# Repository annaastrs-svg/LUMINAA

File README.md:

LUMINA

SEE PAG !
https://annaastrs-svg.github.io/Lumina-Pag-/

Lumina is a little friend with a module to measure your pulse per minute! It tells you if you're okay, 
if you're very relaxed, or if you're very agitated.

I made this little Tamagotchi pulse meter because I found an oximeter that didn't work at my house,
so I opened it up and tried to make it work with my ESP. I used the TX and it worked, but not in the way I wanted.
I ended up buying an Arduino MAX pulse meter and created this little Tamagotchi, which I named Lumina. 
It's like a little keychain that helps you and measures your pulse and acts based on that.

! DEMO ! 
! TRY IT ! 
it works by u putting ur emotion on the terminal.
its in spanish btw....

https://wokwi.com/projects/463667608955522049

PCB ! 

BOM ! 

 WIRES ! 

 ESP32 - MAX

 3V3 - VIN
 GND - GND
  21 - SCL 
  22 - SDA

 ESP32 - BUZZER

GND - GND
D5 - S
 
 ESP32 - OLED 0.96
 
 3V3 - 3V3
 GND - GND
 21 - SDA
22 -  SCK

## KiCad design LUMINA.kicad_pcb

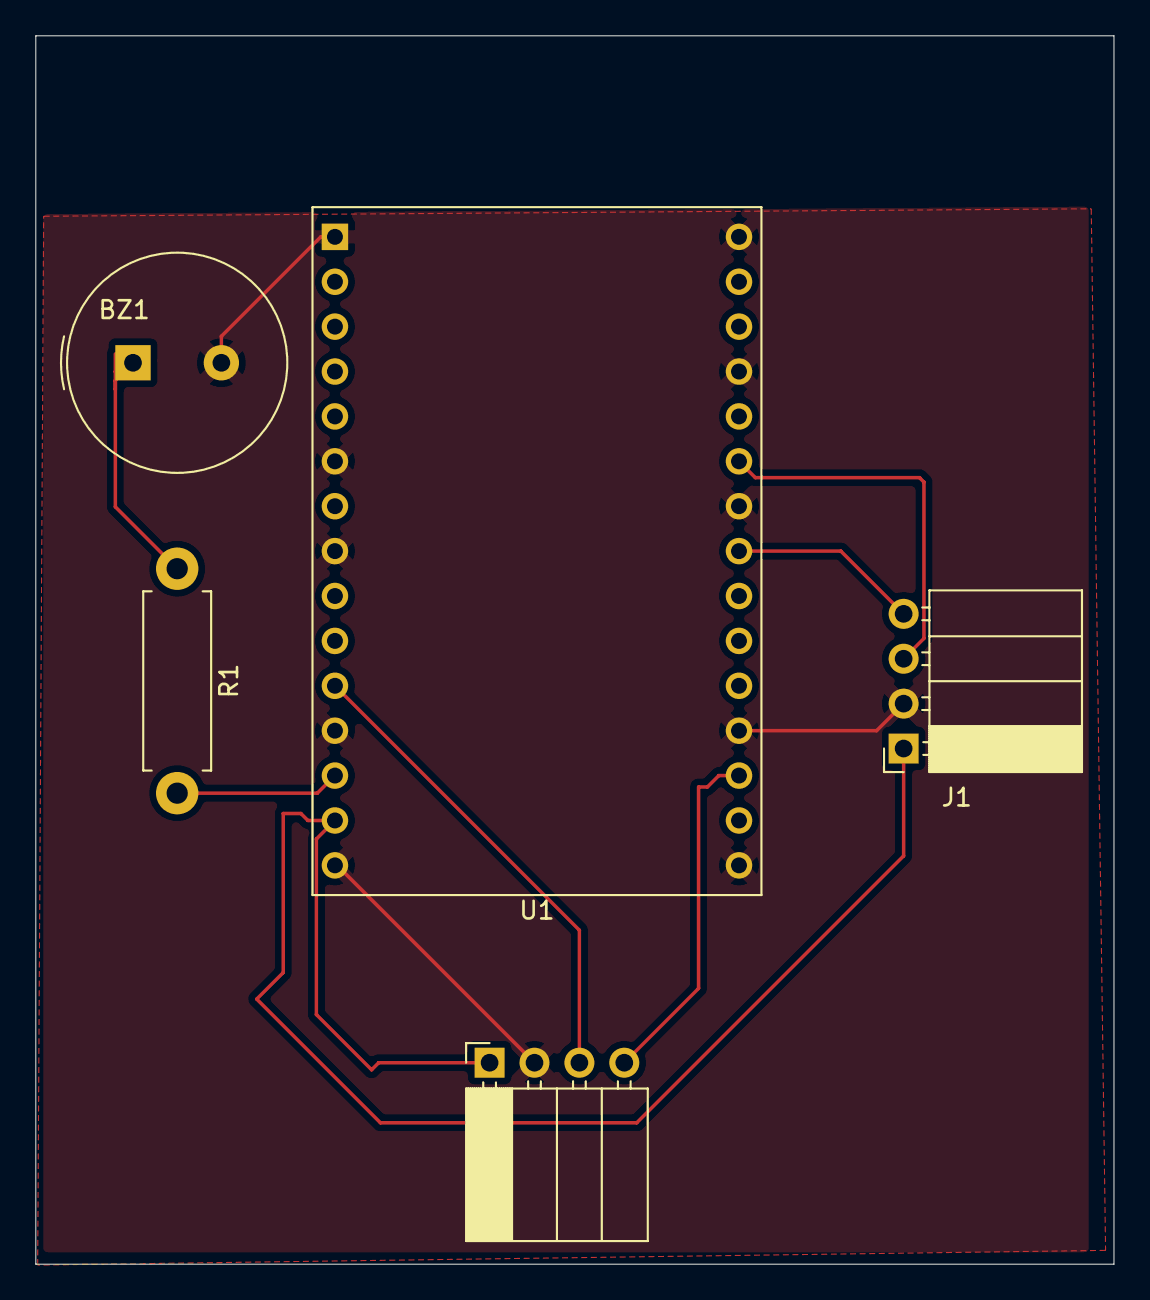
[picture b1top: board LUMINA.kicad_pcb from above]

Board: 2 copper layers, 61.0 x 69.5 mm, 5 parts (0 on the bottom side), 7 nets.

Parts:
BZ1: Buzzer; Buzzer_TDK_PS1240P02BT_D12.2mm_H6.5mm
J1, J2: Conn_01x04_Socket; PinSocket_1x04_P2.54mm_Horizontal
R1: 100; R_Axial_DIN0411_L9.9mm_D3.6mm_P12.70mm_Horizontal
U1: ESP32-C3-DevKitM-1

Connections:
+3V3: J1.1, J2.1, R1.2, U1.13 (5V), U1.14 (5V)
GND: BZ1.2 (-), J1.2, J2.2, U1.1 (GND), U1.6 (GND), U1.8 (GND), U1.12 (GND), U1.15 (GND), U1.16 (GND), U1.19 (GND), U1.24 (GND), U1.27 (GND), U1.30 (GND)
unnamed: BZ1.1 (+), R1.1
unnamed: J1.3, U1.25 (IO8)
unnamed: J1.4, U1.23 (IO7)
unnamed: J2.3, U1.11 (IO10)
unnamed: J2.4, U1.18 (IO18)

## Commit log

2026-06-12 Gerber. zip
2026-06-12 CAD . STEP
2026-06-12 CODE . INO
2026-06-12 KiCad Board 10.0
2026-06-12 KiCad Project 10.0
2026-06-12 KiCad Schematic !
2026-06-12 BOM.csv
2026-06-12 Create README.md for Lumina pulse meter project
    Added a README file with project details and images.
2026-06-12 BOM . CSV
    I think its in table format :,c idk what u wanna say with table format... its in a table .csv with coma separated
2026-06-12 README.md chek upload bom and
    please please please tell me i did it right with the bom cus i dont understand whats wrong with it :C
2026-06-12 Delete BOM.csv ....
    JEJE ill put links
2026-06-12 BOM . CSV
    i puted links! (thanks benny )
2026-06-19 Add project page link to README
    Added a link to the project page.
